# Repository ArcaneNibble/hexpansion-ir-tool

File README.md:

# EMFCamp Hexpansion -- PY32 and infrared remote control

38 kHz consumer infrared TX/RX, proving ground for Puya PY32 microcontroller

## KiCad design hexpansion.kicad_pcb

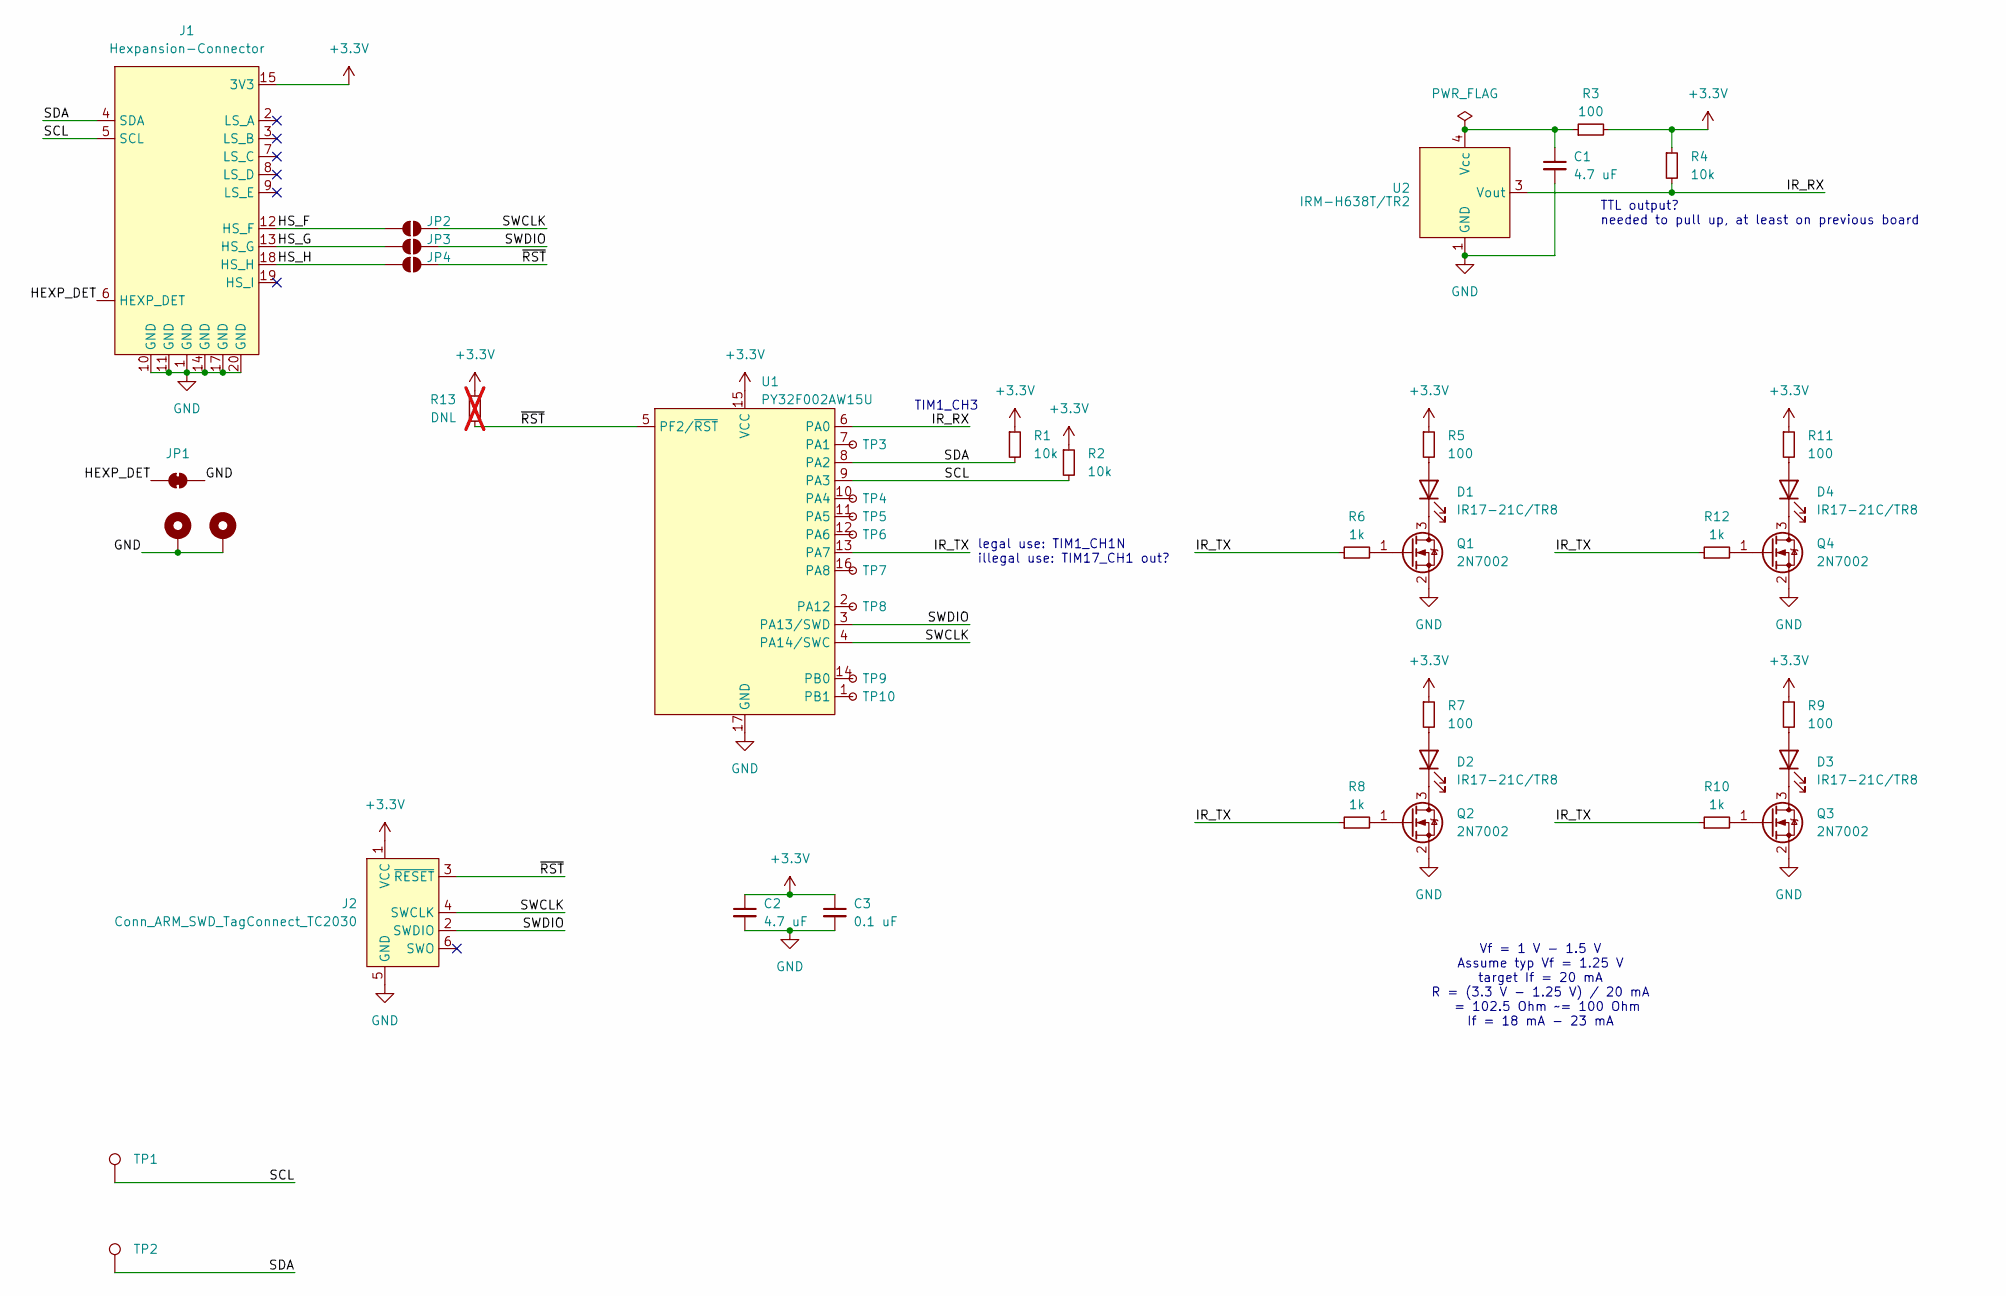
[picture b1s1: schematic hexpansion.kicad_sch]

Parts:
C1, C2: 4.7 uF; C_0805_2012Metric; LCSC C1779
C3: 0.1 uF; C_0402_1005Metric; LCSC C1525
D1, D2, D3, D4: IR17-21C/TR8; LED_0805_2012Metric; LCSC C131250
H1, H2: MountingHole_Pad; MountingHole_2.2mm_M2_Pad_Via
J1: Hexpansion-Connector; hexpansion-edge-connector
J2: Conn_ARM_SWD_TagConnect_TC2030; Tag-Connect_TC2030-IDC-FP_2x03_P1.27mm_Vertical
JP1: SolderJumper_2_Bridged; SolderJumper-2_P1.3mm_Bridged_RoundedPad1.0x1.5mm
JP2: SWCLK; SolderJumper-2_P1.3mm_Open_RoundedPad1.0x1.5mm
JP3: SWDIO; SolderJumper-2_P1.3mm_Open_RoundedPad1.0x1.5mm
JP4: ~{RST}; SolderJumper-2_P1.3mm_Open_RoundedPad1.0x1.5mm
Q1, Q2, Q3, Q4: 2N7002; SOT-23; LCSC C7420321
R1, R2, R4: 10k; R_0402_1005Metric; LCSC C25744
R3, R5, R7, R9, R11: 100; R_0805_2012Metric; LCSC C17408
R6, R8, R10, R12: 1k; R_0402_1005Metric; LCSC C11702
R13: DNL; R_0402_1005Metric; not fitted
TP1: SCL; TestPoint_Pad_2.0x2.0mm
TP2: SDA; TestPoint_Pad_2.0x2.0mm
TP3: PA1; TestPoint_Pad_1.0x1.0mm
TP4: PA4; TestPoint_Pad_1.0x1.0mm
TP5: PA5; TestPoint_Pad_1.0x1.0mm
TP6: PA6; TestPoint_Pad_1.0x1.0mm
TP7: PA8; TestPoint_Pad_1.0x1.0mm
TP8: PA12; TestPoint_Pad_1.0x1.0mm
TP9: PB0; TestPoint_Pad_1.0x1.0mm
TP10: PB1; TestPoint_Pad_1.0x1.0mm
U1: PY32F002AW15U; QFN-16-1EP_3x3mm_P0.5mm_EP1.7x1.7mm; LCSC C5291740
U2: IRM-H638T/TR2; IRM-H6XXT; LCSC C91447

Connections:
+3.3V: C2.1, C3.1, J1.15 (3V3), J1.16 (3V3), J2.1 (VCC), R1.1, R2.1, R3.2, R4.1, R5.1, R7.1, R9.1, R11.1, R13.1, U1.15 (VCC)
/HEXP_DET: J1.6 (HEXP_DET), JP1.1 (A)
/HS_F: J1.12 (HS_F), JP2.1 (A)
/HS_G: J1.13 (HS_G), JP3.1 (A)
/HS_H: J1.18 (HS_H), JP4.1 (A)
/IR_RX: R4.2, U1.6 (PA0), U2.3 (Vout)
/IR_TX: R6.1, R8.1, R10.1, R12.1, U1.13 (PA7)
/SCL: J1.5 (SCL), R2.2, TP1.1, U1.9 (PA3)
/SDA: J1.4 (SDA), R1.2, TP2.1, U1.8 (PA2)
/SWCLK: J2.4 (SWCLK), JP2.2 (B), U1.4 (PA14/SWC)
/SWDIO: J2.2 (SWDIO), JP3.2 (B), U1.3 (PA13/SWD)
/~RST: J2.3 (~RESET), JP4.2 (B), R13.2, U1.5 (PF2/~RST)
GND: C1.2, C2.2, C3.2, H1.1, H2.1, J1.1 (GND), J1.10 (GND), J1.11 (GND), J1.14 (GND), J1.17 (GND), J1.20 (GND), J2.5 (GND), JP1.2 (B), Q1.2 (S), Q2.2 (S), Q3.2 (S), Q4.2 (S), U1.17 (GND), U2.1 (GND), U2.2 (GND)
unnamed: D1.2 (A), R5.2
unnamed: D1.1 (K), Q1.3 (D)
unnamed: D2.2 (A), R7.2
unnamed: D2.1 (K), Q2.3 (D)
unnamed: D3.2 (A), R9.2
unnamed: D3.1 (K), Q3.3 (D)
unnamed: D4.2 (A), R11.2
unnamed: D4.1 (K), Q4.3 (D)
unnamed: Q1.1 (G), R6.2
unnamed: Q2.1 (G), R8.2
unnamed: Q3.1 (G), R10.2
unnamed: Q4.1 (G), R12.2
unnamed: TP3.1, U1.7 (PA1)
unnamed: TP4.1, U1.10 (PA4)
unnamed: TP5.1, U1.11 (PA5)
unnamed: TP6.1, U1.12 (PA6)
unnamed: TP7.1, U1.16 (PA8)
unnamed: TP8.1, U1.2 (PA12)
unnamed: TP9.1, U1.14 (PB0)
unnamed: TP10.1, U1.1 (PB1)
unnamed: C1.1, R3.1, U2.4 (Vcc)

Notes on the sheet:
TTL output? needed to pull up, at least on previous board
Vf = 1 V - 1.5 V Assume typ Vf = 1.25 V target If = 20 mA R = (3.3 V - 1.25 V) / 20 mA = 102.5 Ohm ~= 100 Ohm If = 18 mA - 23 mA
TIM1_CH3
legal use: TIM1_CH1N illegal use: TIM17_CH1 out?

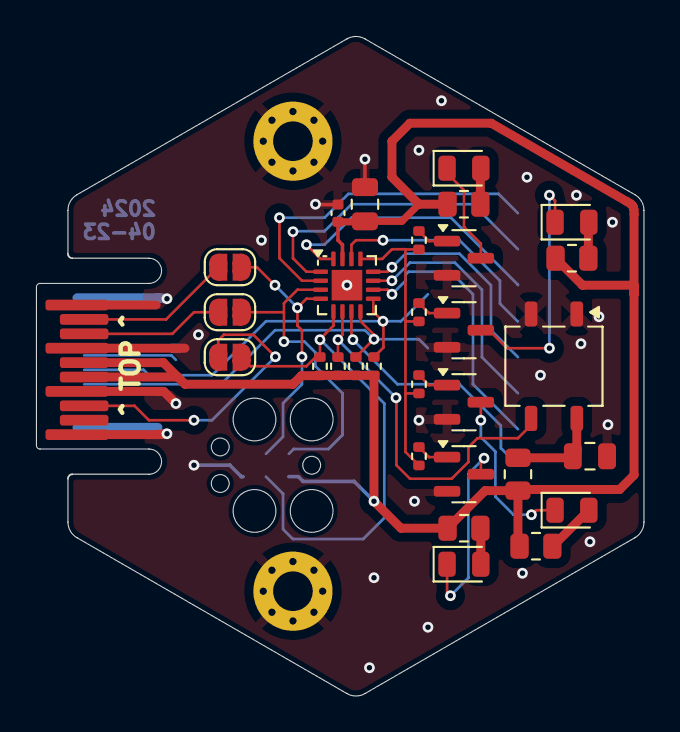
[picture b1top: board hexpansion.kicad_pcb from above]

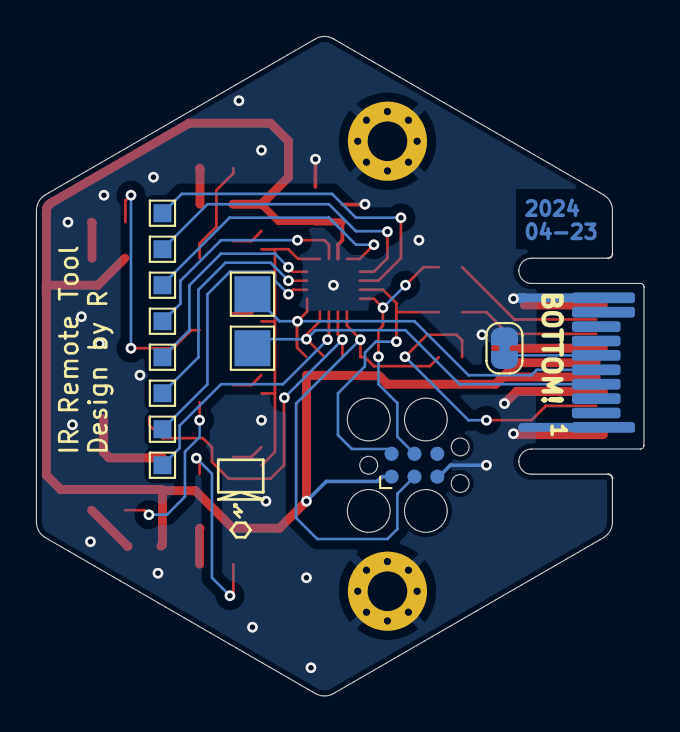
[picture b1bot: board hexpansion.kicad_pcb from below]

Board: 2 copper layers, 33.7 x 36.6 mm, 44 parts (12 on the bottom side), 34 nets.

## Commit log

2024-04-03 add py32 sym
2024-04-03 copy irm ir module symbol
2024-04-03 fix pin ordering
2024-04-03 mark gnd as power in
2024-04-03 first pass at sch
2024-04-03 fixes, some footprints
2024-04-03 copy IR rx footprint
2024-04-03 assign footprints
2024-04-03 rough place of pcb
2024-04-03 setup board, rough place
2024-04-04 routing tweaks
2024-04-04 clean up silk/fab
2024-04-23 add LCSC part numbers
2024-04-23 transfer LCSC fields to PCB
2024-04-23 some pcb doodles
2024-04-23 cleanups for bom/fab/etc output
2024-04-23 xxx yyy
2024-04-24 Add rev A schematic as PDF
2024-09-04 Add README
2024-09-04 oh wait, there was already a license
